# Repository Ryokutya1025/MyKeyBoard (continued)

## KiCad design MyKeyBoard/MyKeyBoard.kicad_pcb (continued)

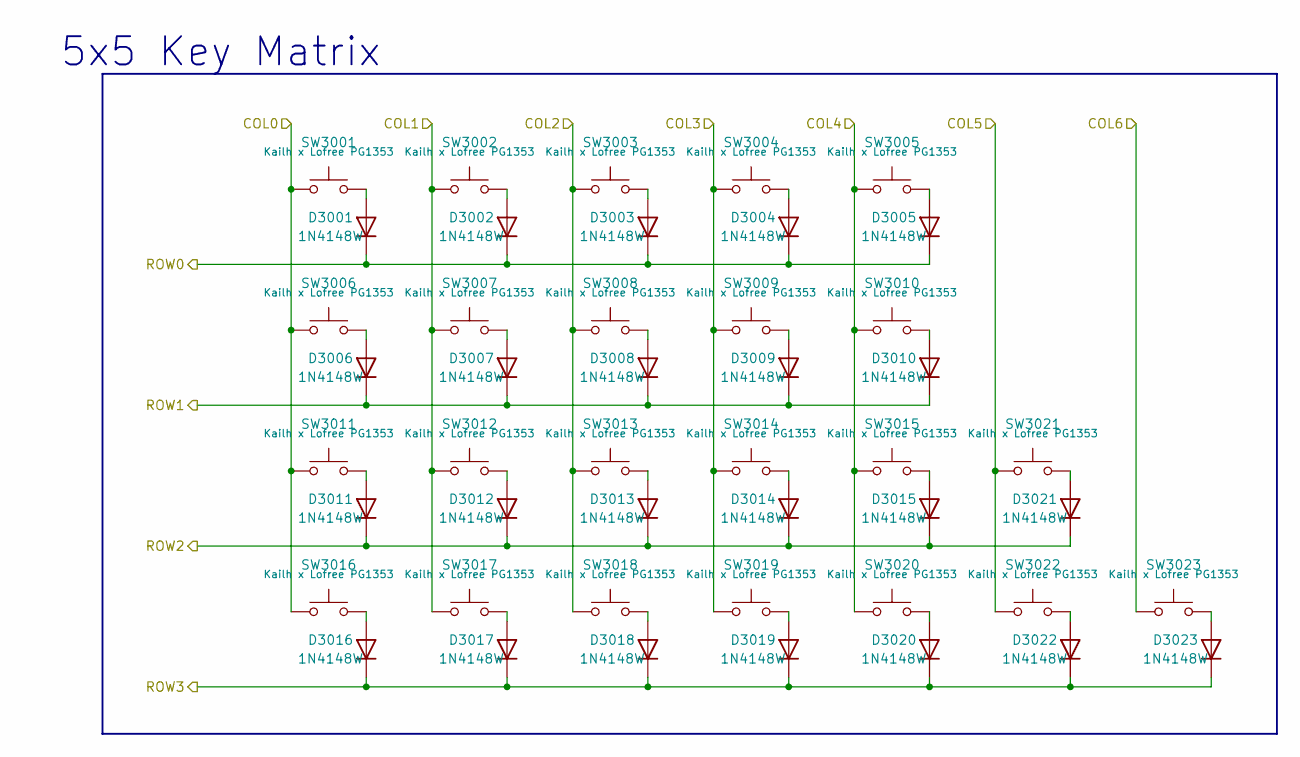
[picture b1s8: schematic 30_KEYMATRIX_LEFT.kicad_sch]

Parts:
D3001, D3002, D3003, D3004, D3005, D3006, D3007, D3008, D3009, D3010, D3011, D3012, D3013, D3014, D3015, D3016, D3017, D3018, D3019, D3020, D3021, D3022, D3023: 1N4148W; D_SOD-123
SW3001, SW3002, SW3003, SW3004, SW3005, SW3006, SW3007, SW3008, SW3009, SW3010, SW3011, SW3012, SW3013, SW3014, SW3015, SW3016, SW3017, SW3018, SW3019, SW3020, SW3021, SW3022, SW3023: Kailh x Lofree PG1353; Kailh-PG1353-Hotswap-1U

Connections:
/COL0_LEFT: SW3001.1, SW3006.1, SW3011.1, SW3016.1; also elsewhere on the board
/COL1_LEFT: SW3002.1, SW3007.1, SW3012.1, SW3017.1; also elsewhere on the board
/COL2_LEFT: SW3003.1, SW3008.1, SW3013.1, SW3018.1; also elsewhere on the board
/COL3_LEFT: SW3004.1, SW3009.1, SW3014.1, SW3019.1; also elsewhere on the board
/COL4_LEFT: SW3005.1, SW3010.1, SW3015.1, SW3020.1; also elsewhere on the board
/COL5_LEFT: SW3021.1, SW3022.1; also elsewhere on the board
/COL6_LEFT: SW3023.1; also elsewhere on the board
/ROW0_LEFT: D3001.1 (K), D3002.1 (K), D3003.1 (K), D3004.1 (K), D3005.1 (K); also elsewhere on the board
/ROW1_LEFT: D3006.1 (K), D3007.1 (K), D3008.1 (K), D3009.1 (K), D3010.1 (K); also elsewhere on the board
/ROW2_LEFT: D3011.1 (K), D3012.1 (K), D3013.1 (K), D3014.1 (K), D3015.1 (K), D3021.1 (K); also elsewhere on the board
/ROW3_LEFT: D3016.1 (K), D3017.1 (K), D3018.1 (K), D3019.1 (K), D3020.1 (K), D3022.1 (K), D3023.1 (K); also elsewhere on the board
unnamed: D3001.2 (A), SW3001.2
unnamed: D3002.2 (A), SW3002.2
unnamed: D3003.2 (A), SW3003.2
unnamed: D3004.2 (A), SW3004.2
unnamed: D3005.2 (A), SW3005.2
unnamed: D3006.2 (A), SW3006.2
unnamed: D3007.2 (A), SW3007.2
unnamed: D3008.2 (A), SW3008.2
unnamed: D3009.2 (A), SW3009.2
unnamed: D3010.2 (A), SW3010.2
unnamed: D3011.2 (A), SW3011.2
unnamed: D3012.2 (A), SW3012.2
unnamed: D3013.2 (A), SW3013.2
unnamed: D3014.2 (A), SW3014.2
unnamed: D3015.2 (A), SW3015.2
unnamed: D3016.2 (A), SW3016.2
unnamed: D3017.2 (A), SW3017.2
unnamed: D3018.2 (A), SW3018.2
unnamed: D3019.2 (A), SW3019.2
unnamed: D3020.2 (A), SW3020.2
unnamed: D3021.2 (A), SW3021.2
unnamed: D3022.2 (A), SW3022.2
unnamed: D3023.2 (A), SW3023.2

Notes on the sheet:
5x5 Key Matrix

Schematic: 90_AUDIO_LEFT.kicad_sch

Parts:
C9001: 10µF; C_0805_2012Metric
C9002: 100nF; C_0603_1608Metric
J9001: To Speaker; JST_SH_SM02B-SRSS-TB_1x02-1MP_P1.00mm_Horizontal_ToSpeaker
R9001: 1kΩ; R_0603_1608Metric
U9001: MAX98357A; TQFN-16-1EP_3x3mm_P0.5mm_EP1.23x1.23mm

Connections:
/+4V0_LEFT: C9001.1, C9002.1, U9001.7 (VDD), U9001.8 (VDD); also elsewhere on the board
/AUDIO_BCLK_LEFT: U9001.16 (BCLK); also elsewhere on the board
/AUDIO_DOUT_LEFT: U9001.1 (DIN); also elsewhere on the board
/AUDIO_LRCLK_LEFT: U9001.14 (LRCLK); also elsewhere on the board
/AUDIO_SD_LEFT: R9001.1; also elsewhere on the board
GND: C9001.2, C9002.2, U9001.3 (GND), U9001.11 (GND), U9001.15 (GND), U9001.17 (PAD); also elsewhere on the board
unnamed: J9001.1, U9001.9 (OUTP)
unnamed: J9001.2, U9001.10 (OUTN)
unnamed: R9001.2, U9001.4 (~SD_MODE)

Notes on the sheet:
Audio Amplifier

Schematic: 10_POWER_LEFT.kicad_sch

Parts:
C1001, C1002: 1µF; C_0603_1608Metric
C1003: 4.7µF; C_0805_2012Metric
C1004, C1005, C1007: 10µF; C_0805_2012Metric
C1006: 1nF; C_0603_1608Metric
C1008, C1009: 22µF; C_1206_3216Metric
C1010: 47µF; C_1210_3225Metric
C1011, C1012: 0.1µF; C_0603_1608Metric
D1001: LED_Dual_KAK; LED_LiteOn_LTST-S326
D1002: RED_LED; LED_0603_1608Metric
J1001: Battery; JST_PH_S3B-PH-SM4-TB_1x03-1MP_P2.00mm_Horizontal
J1002: USB_C_Receptacle_USB2.0_16P; USB_C_Receptacle_GCT_USB4105-xx-A_16P_TopMnt_Horizontal
L1001: 2.2µH; L_1008_2520Metric
L1002: 1µH; L_1008_2520Metric
Q1001: 2N7002; SOT-23
R1001, R1002, R1009: 1.5kΩ; R_0603_1608Metric
R1003, R1004: 5.1kΩ; R_0603_1608Metric
R1005, R1006: 27Ω; R_0603_1608Metric
R1007: 3.09kΩ; R_0603_1608Metric
R1008: 2.21kΩ; R_0603_1608Metric
R1010, R1015: 0Ω; R_0603_1608Metric
R1011, R1018: 1MΩ; R_0603_1608Metric
R1012: 100kΩ; R_0603_1608Metric
R1013: 634kΩ; R_0603_1608Metric
R1014: 16.2kΩ; R_0603_1608Metric
R1016: 36.5kΩ; R_0603_1608Metric
R1017: 91kΩ; R_0603_1608Metric
S1001: JS102011SAQN; SW_JS102011SAQN; DigiKey_Part_Number 401-1999-1-ND
TP1001: TP_3V3_LEFT; TestPoint_Pad_D1.5mm
U1001: TPS22919DCKR; MPN TPS22919DCKR
U1002: BQ24074RGT
U1003: TPD2E2U06DCK; SOT-323_SC-70
U1004: TPS631000DRLR; TPS631000DRLR_TEX-L
U1005: TPS63900; WSON-10-1EP_2.5x2.5mm_P0.5mm_EP1.2x2mm_ThermalVias
U1006: TXU0101DCKR; SC70-6_DCK_TEX

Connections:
/10_POWER_LEFT/BAT_NTC: J1001.2, U1002.1 (TS)
/10_POWER_LEFT/CHG_N: R1001.2, U1002.9 (~CHG)
/10_POWER_LEFT/PGOOD_N: R1002.2, U1002.7 (~PGOOD)
/10_POWER_LEFT/PWR_EN: R1018.2, S1001.2, U1004.5 (EN), U1005.1 (EN)
/10_POWER_LEFT/RGB_DATA_LED_LEFT: U1006.4 (BY); also elsewhere on the board
/10_POWER_LEFT/SYS_RAW: C1004.1, C1007.1, C1009.1, D1001.2 (A), S1001.3, U1002.10 (OUT), U1002.11 (OUT), U1004.4 (VIN), U1005.10 (VIN)
/10_POWER_LEFT/USB_SHIELD: C1006.2, J1002.SH (SHIELD), R1010.1, R1011.2
/+3V3_LEFT: C1008.1, C1011.1, R1009.1, TP1001.1 (1_1), U1005.6 (VOUT), U1006.1 (VCCA); also elsewhere on the board
/+4V0_LEFT: C1001.1, C1010.1, R1013.2, U1001.1 (VIN), U1004.1 (VOUT); also elsewhere on the board
/LOW_BAT_LED_LEFT: Q1001.1 (G), R1012.1; also elsewhere on the board
/RGB_DATA_MCU_LEFT: U1006.3 (A); also elsewhere on the board
/RGB_EN_LEFT: U1001.3 (ON), U1006.5 (OE); also elsewhere on the board
/RGB_VDD_LEFT: C1012.1, U1001.5 (QOD), U1001.6 (VOUT), U1006.6 (VCCB); also elsewhere on the board
/USB_DM_LEFT: R1005.2; also elsewhere on the board
/USB_DP_LEFT: R1006.1; also elsewhere on the board
/VBAT_LEFT: C1005.1, J1001.1, U1002.2 (BAT), U1002.3 (BAT); also elsewhere on the board
/VBUS_5V_LEFT: C1002.1, C1003.1, J1002.A4 (VBUS), J1002.A9 (VBUS), J1002.B4 (VBUS), J1002.B9 (VBUS), U1002.6 (EN1), U1002.13 (IN); also elsewhere on the board
GND: C1001.2, C1002.2, C1003.2, C1004.2, C1005.2, C1006.1, C1007.2, C1008.2, C1009.2, C1010.2, C1011.2, C1012.2, J1001.3, J1002.A1 (GND), J1002.A12 (GND), J1002.B1 (GND), J1002.B12 (GND), Q1001.2 (S), R1003.2, R1004.2, R1007.1, R1008.1, R1010.2, R1011.1, R1012.2, R1014.1, R1015.1, R1016.1, R1017.2, R1018.1, S1001.1, U1001.2 (GND), U1002.4 (~CE), U1002.5 (EN2), U1002.8 (VSS), U1002.17 (VSS), U1003.3, U1004.6 (MODE), U1004.7 (GND), U1005.2 (SEL), U1005.8 (GND), U1005.11 (GND), U1006.2 (GND); also elsewhere on the board
unnamed: D1001.1 (K1), R1001.1
unnamed: D1001.3 (K2), R1002.1
unnamed: D1002.2 (A), R1009.2
unnamed: D1002.1 (K), Q1001.3 (D)
unnamed: J1002.A5 (CC1), R1003.1
unnamed: J1002.B5 (CC2), R1004.1
unnamed: J1002.A6 (D+), J1002.B6 (D+), R1006.2, U1003.1
unnamed: J1002.A7 (D-), J1002.B7 (D-), R1005.1, U1003.2
unnamed: R1007.2, U1002.12 (ILIM)
unnamed: R1008.2, U1002.16 (ISET)
unnamed: R1013.1, R1017.1, U1004.8 (FB)
unnamed: L1002.1, U1004.3 (LX1)
unnamed: L1002.2, U1004.2 (LX2)
unnamed: R1016.2, U1005.3 (CFG1)
unnamed: R1015.2, U1005.4 (CFG2)
unnamed: R1014.2, U1005.5 (CFG3)
unnamed: L1001.1, U1005.9 (LX1)
unnamed: L1001.2, U1005.7 (LX2)

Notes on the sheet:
Battery Charger / Power Path
RGB Power Switch
USB Input / Protection
Main Power Switch
Main 3.3V Power
Low Battery LED
RGB 4.0V Power
Charge Status LED
RGB DATA Level Shifter

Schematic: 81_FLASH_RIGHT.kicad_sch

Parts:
C8101: 100nF; C_0603_1608Metric
R8101: 10kΩ; R_0603_1608Metric
U8101: W25Q512JVEIQ; PARTREV G; DigiKey_Part_Number 256-W25Q512JVEIQ-TUBE-ND

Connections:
/+3V3_RIGHT: C8101.1, R8101.1, U8101.8 (VCC); also elsewhere on the board
/FLASH_CLK_RIGHT: U8101.6 (CLK); also elsewhere on the board
/FLASH_CS_RIGHT: R8101.2, U8101.1 (~CS); also elsewhere on the board
/FLASH_I0_RIGHT: U8101.5 (IO0/DI); also elsewhere on the board
/FLASH_I1_RIGHT: U8101.2 (IO1/DO); also elsewhere on the board
/FLASH_I2_RIGHT: U8101.3 (IO2/~WP); also elsewhere on the board
/FLASH_I3_RIGHT: U8101.7 (IO3/~HOLD/~RESET); also elsewhere on the board
GND: C8101.2, U8101.4 (GND), U8101.9 (EXP); also elsewhere on the board

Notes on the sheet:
External Flash Memory

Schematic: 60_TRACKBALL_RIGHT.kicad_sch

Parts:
C6101: 3.3µF / 16V X7R; C_0805_2012Metric
C6102, C6103, C6104: 100nF X7R; C_0603_1608Metric
C6105: 10nF X7R; C_0603_1608Metric
C6106: 10nF; C_0603_1608Metric
C6107: 10µF; C_0805_2012Metric
TP6101: TP_TRACK_NRESET; TestPoint_Pad_D1.5mm
TP6102: TP_TRACK_MOTION; TestPoint_Pad_D1.5mm
TP6103: TP_TRACK_SCLK; TestPoint_Pad_D1.5mm
TP6104: TP_TRACK_SDIO; TestPoint_Pad_D1.5mm
TP6105: TP_TRACK_NCS; TestPoint_Pad_D1.5mm
U6101: PMW3610; PMW3610DM-SUDU 16Pin

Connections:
+1V8: C6101.1, C6102.1, U6101.14 (VDD); also elsewhere on the board
/+3V3_RIGHT: C6103.1, U6101.6 (VDDIO); also elsewhere on the board
/TRACK_MOTION: TP6102.1 (1_1), U6101.8 (MOTION); also elsewhere on the board
/TRACK_NCS: TP6105.1 (1_1), U6101.5 (NCS); also elsewhere on the board
/TRACK_NRESET: TP6101.1 (1_1), U6101.7 (NRESET); also elsewhere on the board
/TRACK_SCLK: TP6103.1 (1_1), U6101.3 (SCLK); also elsewhere on the board
/TRACK_SDIO: TP6104.1 (1_1), U6101.2 (SDIO); also elsewhere on the board
GND: C6101.2, C6102.2, C6103.2, C6105.2, C6106.2, C6107.2, U6101.11 (GND); also elsewhere on the board
unnamed: C6105.1, U6101.1 (+VCSEL), U6101.10 (PASS_T)
unnamed: U6101.15 (XYLASER), U6101.16 (-VCSEL)
unnamed: C6104.1, U6101.13 (CN)
unnamed: C6104.2, U6101.12 (CP)
unnamed: C6106.1, C6107.1, U6101.9 (VCP)

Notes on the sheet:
Trackball Sensor

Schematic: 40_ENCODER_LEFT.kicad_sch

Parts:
C4001, C4002, C4003: 10nF; C_0603_1608Metric
R4001, R4003, R4006: 10kΩ; R_0603_1608Metric
R4002, R4004, R4005: 1kΩ; R_0603_1608Metric
SW4001: SKQYACE010
SW4002: RotaryEncoder; EC05E1220202

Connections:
/+3V3_LEFT: R4001.2, R4003.1, R4006.1; also elsewhere on the board
/ENC_A_LEFT: C4003.1, R4004.1; also elsewhere on the board
/ENC_B_LEFT: C4002.1, R4005.1; also elsewhere on the board
/ENC_SW_LEFT: C4001.1, R4001.1, R4002.1; also elsewhere on the board
GND: C4001.2, C4002.2, C4003.2, SW4001.2, SW4002.C; also elsewhere on the board
unnamed: R4002.2, SW4001.1
unnamed: R4003.2, R4004.2, SW4002.A
unnamed: R4005.2, R4006.2, SW4002.B

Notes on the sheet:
Horizontal Encoder + Click

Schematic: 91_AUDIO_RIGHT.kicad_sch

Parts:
C9101: 10µF; C_0805_2012Metric
C9102: 100nF; C_0603_1608Metric
J9101: To Speaker; JST_SH_SM02B-SRSS-TB_1x02-1MP_P1.00mm_Horizontal_ToSpeaker
R9101: 1kΩ; R_0603_1608Metric
U9101: MAX98357A; TQFN-16-1EP_3x3mm_P0.5mm_EP1.23x1.23mm

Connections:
/+4V0_RIGHT: C9101.1, C9102.1, U9101.7 (VDD), U9101.8 (VDD); also elsewhere on the board
/AUDIO_BCLK_RIGHT: U9101.16 (BCLK); also elsewhere on the board
/AUDIO_DOUT_RIGHT: U9101.1 (DIN); also elsewhere on the board
/AUDIO_LRCLK_RIGHT: U9101.14 (LRCLK); also elsewhere on the board
/AUDIO_SD_RIGHT: R9101.1; also elsewhere on the board
GND: C9101.2, C9102.2, U9101.3 (GND), U9101.11 (GND), U9101.15 (GND), U9101.17 (PAD); also elsewhere on the board
unnamed: J9101.1, U9101.9 (OUTP)
unnamed: J9101.2, U9101.10 (OUTN)
unnamed: R9101.2, U9101.4 (~SD_MODE)

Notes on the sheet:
Audio Amplifier

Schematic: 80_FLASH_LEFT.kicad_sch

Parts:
C8001: 100nF; C_0603_1608Metric
R8001: 10kΩ; R_0603_1608Metric
U8001: W25Q512JVEIQ; PARTREV G; DigiKey_Part_Number 256-W25Q512JVEIQ-TUBE-ND

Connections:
/+3V3_LEFT: C8001.1, R8001.1, U8001.8 (VCC); also elsewhere on the board
/FLASH_CLK_LEFT: U8001.6 (CLK); also elsewhere on the board
/FLASH_CS_LEFT: R8001.2, U8001.1 (~CS); also elsewhere on the board
/FLASH_I0_LEFT: U8001.5 (IO0/DI); also elsewhere on the board
/FLASH_I1_LEFT: U8001.2 (IO1/DO); also elsewhere on the board
/FLASH_I2_LEFT: U8001.3 (IO2/~WP); also elsewhere on the board
/FLASH_I3_LEFT: U8001.7 (IO3/~HOLD/~RESET); also elsewhere on the board
GND: C8001.2, U8001.4 (GND), U8001.9 (EXP); also elsewhere on the board

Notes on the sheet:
External Flash Memory

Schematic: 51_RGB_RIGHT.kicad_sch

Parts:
C5101: 47µF; C_1210_3225Metric
C5102, C5103, C5104, C5105, C5106, C5107, C5108, C5109, C5110, C5111, C5112, C5113, C5114, C5115, C5116, C5117, C5118, C5119, C5120, C5121, C5122: 100nF; C_0603_1608Metric
D5101, D5102, D5103, D5104, D5105, D5106, D5107, D5108, D5109, D5110, D5111, D5112, D5113, D5114, D5115, D5116, D5117, D5118, D5119, D5120, D5121: SK6805MINI-E; SK6812MINI-E
R5101: 100Ω; R_0603_1608Metric

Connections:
/11_POWER_RIGHT/RGB_DATA_LED_RIGHT: R5101.1; also elsewhere on the board
/51_RGB_RIGHT/RGB_DATA_08to09: D5108.4 (DOUT), D5109.2 (DIN)
/51_RGB_RIGHT/RGB_DATA_16to17: D5116.4 (DOUT), D5117.2 (DIN)
/RGB_VDD_RIGHT: C5101.1, C5102.1, C5103.1, C5104.1, C5105.1, C5106.1, C5107.1, C5108.1, C5109.1, C5110.1, C5111.1, C5112.1, C5113.1, C5114.1, C5115.1, C5116.1, C5117.1, C5118.1, C5119.1, C5120.1, C5121.1, C5122.1, D5101.3 (VDD), D5102.3 (VDD), D5103.3 (VDD), D5104.3 (VDD), D5105.3 (VDD), D5106.3 (VDD), D5107.3 (VDD), D5108.3 (VDD), D5109.3 (VDD), D5110.3 (VDD), D5111.3 (VDD), D5112.3 (VDD), D5113.3 (VDD), D5114.3 (VDD), D5115.3 (VDD), D5116.3 (VDD), D5117.3 (VDD), D5118.3 (VDD), D5119.3 (VDD), D5120.3 (VDD), D5121.3 (VDD); also elsewhere on the board
GND: C5101.2, C5102.2, C5103.2, C5104.2, C5105.2, C5106.2, C5107.2, C5108.2, C5109.2, C5110.2, C5111.2, C5112.2, C5113.2, C5114.2, C5115.2, C5116.2, C5117.2, C5118.2, C5119.2, C5120.2, C5121.2, C5122.2, D5101.1 (VSS), D5102.1 (VSS), D5103.1 (VSS), D5104.1 (VSS), D5105.1 (VSS), D5106.1 (VSS), D5107.1 (VSS), D5108.1 (VSS), D5109.1 (VSS), D5110.1 (VSS), D5111.1 (VSS), D5112.1 (VSS), D5113.1 (VSS), D5114.1 (VSS), D5115.1 (VSS), D5116.1 (VSS), D5117.1 (VSS), D5118.1 (VSS), D5119.1 (VSS), D5120.1 (VSS), D5121.1 (VSS); also elsewhere on the board
unnamed: D5101.2 (DIN), R5101.2
unnamed: D5101.4 (DOUT), D5102.2 (DIN)
unnamed: D5102.4 (DOUT), D5103.2 (DIN)
unnamed: D5103.4 (DOUT), D5104.2 (DIN)
unnamed: D5104.4 (DOUT), D5105.2 (DIN)
unnamed: D5105.4 (DOUT), D5106.2 (DIN)
unnamed: D5106.4 (DOUT), D5107.2 (DIN)
unnamed: D5107.4 (DOUT), D5108.2 (DIN)
unnamed: D5109.4 (DOUT), D5110.2 (DIN)
unnamed: D5110.4 (DOUT), D5111.2 (DIN)
unnamed: D5111.4 (DOUT), D5112.2 (DIN)
unnamed: D5112.4 (DOUT), D5113.2 (DIN)
unnamed: D5113.4 (DOUT), D5114.2 (DIN)
unnamed: D5114.4 (DOUT), D5115.2 (DIN)
unnamed: D5115.4 (DOUT), D5116.2 (DIN)
unnamed: D5117.4 (DOUT), D5118.2 (DIN)
unnamed: D5118.4 (DOUT), D5119.2 (DIN)
unnamed: D5119.4 (DOUT), D5120.2 (DIN)
unnamed: D5120.4 (DOUT), D5121.2 (DIN)

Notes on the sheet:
Addressable RGB LED Chain

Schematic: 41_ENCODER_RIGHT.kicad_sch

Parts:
C4101, C4102, C4103: 10nF; C_0603_1608Metric
R4101, R4103, R4106: 10kΩ; R_0603_1608Metric
R4102, R4104, R4105: 1kΩ; R_0603_1608Metric
SW4101: SKQYACE010
SW4102: RotaryEncoder; EC05E1220202

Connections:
/+3V3_RIGHT: R4101.2, R4103.1, R4106.1; also elsewhere on the board
/ENC_A_RIGHT: C4103.1, R4104.1; also elsewhere on the board
/ENC_B_RIGHT: C4102.1, R4105.1; also elsewhere on the board
/ENC_SW_RIGHT: C4101.1, R4101.1, R4102.1; also elsewhere on the board
GND: C4101.2, C4102.2, C4103.2, SW4101.2, SW4102.C; also elsewhere on the board
unnamed: R4102.2, SW4101.1
unnamed: R4103.2, R4104.2, SW4102.A
unnamed: R4105.2, R4106.2, SW4102.B

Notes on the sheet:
Horizontal Encoder + Click

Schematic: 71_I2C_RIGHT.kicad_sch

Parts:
AC7101: LIS2DTW12TR; LGA-12_2x2mm_P0.5mm; Mouser Part Number 511-LIS2DTW12TR
C7101, C7102, C7103, C7104, C7106: 100nF; C_0603_1608Metric
C7105: 10µF; C_0805_2012Metric
R7101, R7102: 3.3kΩ; R_0603_1608Metric
R7103: 10kΩ; R_0603_1608Metric
R7104: 1000Ω; R_0603_1608Metric
U7101: MAX17048G+
U7102: RV-3028-C7

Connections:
/+3V3_RIGHT: AC7101.2 (CS), AC7101.9 (VDD), AC7101.10 (VDDIO), C7101.1, C7104.1, C7105.1, C7106.1, R7101.2, R7102.2, U7102.7 (VDD); also elsewhere on the board
/ACC_INT_RIGHT: AC7101.12 (INT1); also elsewhere on the board
/I2C_SCL_RIGHT: AC7101.1 (SCL/SPC), R7101.1, U7101.7 (SCL), U7102.3 (SCL); also elsewhere on the board
/I2C_SDA_RIGHT: AC7101.4 (SDA/SDI/SDO), R7102.1, U7101.8 (SDA), U7102.4 (SDA); also elsewhere on the board
/VBAT_RIGHT: C7102.1, R7104.2, U7101.2 (CELL), U7101.3 (VDD); also elsewhere on the board
GND: AC7101.3 (SDO/SA0), AC7101.6 (GND_1), AC7101.7 (RES), AC7101.8 (GND_2), C7101.2, C7102.2, C7103.2, C7104.2, C7105.2, C7106.2, R7103.2, U7101.1 (CTG), U7101.4 (GND), U7101.6 (QSTRT), U7101.9 (EPAD), U7102.5 (VSS); also elsewhere on the board
unnamed: R7103.1, U7102.8 (EVI)
unnamed: C7103.1, R7104.1, U7102.6 (VBACKUP)

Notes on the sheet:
RTC and I2C Bus
Motion Sensor
Battery Fuel Gauge

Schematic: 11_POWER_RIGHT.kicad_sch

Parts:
C1101, C1102, C1111, C1112: 1µF; C_0603_1608Metric
C1103: 4.7µF; C_0805_2012Metric
C1104, C1105, C1107: 10µF; C_0805_2012Metric
C1106: 1nF; C_0603_1608Metric
C1108, C1109: 22µF; C_1206_3216Metric
C1110: 47µF; C_1210_3225Metric
C1113, C1114: 0.1µF; C_0603_1608Metric
D1101: LED_Dual_KAK; LED_LiteOn_LTST-S326
D1102: RED_LED; LED_0603_1608Metric
J1101: Battery; JST_PH_S3B-PH-SM4-TB_1x03-1MP_P2.00mm_Horizontal
J1102: USB_C_Receptacle_USB2.0_16P; USB_C_Receptacle_GCT_USB4105-xx-A_16P_TopMnt_Horizontal
L1101: 2.2µH; L_1008_2520Metric
L1102: 1µH; L_1008_2520Metric
Q1101: 2N7002; SOT-23
R1101, R1102, R1109: 1.5kΩ; R_0603_1608Metric
R1103, R1104: 5.1kΩ; R_0603_1608Metric
R1105, R1106: 27Ω; R_0603_1608Metric
R1107: 3.09kΩ; R_0603_1608Metric
R1108: 2.21kΩ; R_0603_1608Metric
R1110, R1115: 0Ω; R_0603_1608Metric
R1111, R1118: 1MΩ; R_0603_1608Metric
R1112: 100kΩ; R_0603_1608Metric
R1113: 634kΩ; R_0603_1608Metric
R1114: 16.2kΩ; R_0603_1608Metric
R1116: 36.5kΩ; R_0603_1608Metric
R1117: 91kΩ; R_0603_1608Metric
S1101: JS102011SAQN; SW_JS102011SAQN; DigiKey_Part_Number 401-1999-1-ND
TP1101: TP_3V3_RIGHT; TestPoint_Pad_D1.5mm
TP1102: TP_1V8_RIGHT; TestPoint_Pad_D1.5mm
U1101: TPS22919DCKR; MPN TPS22919DCKR
U1102: BQ24074RGT
U1103: TPD2E2U06DCK; SOT-323_SC-70
U1104: TPS631000DRLR; TPS631000DRLR_TEX-L
U1105: TLV74318PDBVR
U1106: TPS63900; WSON-10-1EP_2.5x2.5mm_P0.5mm_EP1.2x2mm_ThermalVias
U1107: TXU0101DCKR; SC70-6_DCK_TEX

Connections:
+1V8: C1112.1, TP1102.1 (1_1), U1105.5 (OUT); also elsewhere on the board
/11_POWER_RIGHT/BAT_NTC: J1101.2, U1102.1 (TS)
/11_POWER_RIGHT/CHG_N: R1101.2, U1102.9 (~CHG)
/11_POWER_RIGHT/PGOOD_N: R1102.2, U1102.7 (~PGOOD)
/11_POWER_RIGHT/PWR_EN: R1118.2, S1101.2, U1104.5 (EN), U1106.1 (EN)
/11_POWER_RIGHT/RGB_DATA_LED_RIGHT: U1107.4 (BY); also elsewhere on the board
/11_POWER_RIGHT/SYS_RAW: C1104.1, C1107.1, C1109.1, D1101.2 (A), S1101.3, U1102.10 (OUT), U1102.11 (OUT), U1104.4 (VIN), U1106.10 (VIN)
/11_POWER_RIGHT/USB_SHIELD: C1106.2, J1102.SH (SHIELD), R1110.1, R1111.2
/+3V3_RIGHT: C1108.1, C1111.1, C1113.1, R1109.1, TP1101.1 (1_1), U1105.1 (IN), U1105.3 (EN), U1106.6 (VOUT), U1107.1 (VCCA); also elsewhere on the board
/+4V0_RIGHT: C1101.1, C1110.1, R1113.2, U1101.1 (VIN), U1104.1 (VOUT); also elsewhere on the board
/LOW_BAT_LED_RIGHT: Q1101.1 (G), R1112.1; also elsewhere on the board
/RGB_DATA_MCU_RIGHT: U1107.3 (A); also elsewhere on the board
/RGB_EN_RIGHT: U1101.3 (ON), U1107.5 (OE); also elsewhere on the board
/RGB_VDD_RIGHT: C1114.1, U1101.5 (QOD), U1101.6 (VOUT), U1107.6 (VCCB); also elsewhere on the board
/USB_DM_RIGHT: R1105.2; also elsewhere on the board
/USB_DP_RIGHT: R1106.1; also elsewhere on the board
/VBAT_RIGHT: C1105.1, J1101.1, U1102.2 (BAT), U1102.3 (BAT); also elsewhere on the board
/VBUS_5V_RIGHT: C1102.1, C1103.1, J1102.A4 (VBUS), J1102.A9 (VBUS), J1102.B4 (VBUS), J1102.B9 (VBUS), U1102.6 (EN1), U1102.13 (IN); also elsewhere on the board
GND: C1101.2, C1102.2, C1103.2, C1104.2, C1105.2, C1106.1, C1107.2, C1108.2, C1109.2, C1110.2, C1111.2, C1112.2, C1113.2, C1114.2, J1101.3, J1102.A1 (GND), J1102.A12 (GND), J1102.B1 (GND), J1102.B12 (GND), Q1101.2 (S), R1103.2, R1104.2, R1107.1, R1108.1, R1110.2, R1111.1, R1112.2, R1114.1, R1115.1, R1116.1, R1117.2, R1118.1, S1101.1, U1101.2 (GND), U1102.4 (~CE), U1102.5 (EN2), U1102.8 (VSS), U1102.17 (VSS), U1103.3, U1104.6 (MODE), U1104.7 (GND), U1105.2 (GND), U1106.2 (SEL), U1106.8 (GND), U1106.11 (GND), U1107.2 (GND); also elsewhere on the board
unnamed: D1101.1 (K1), R1101.1
unnamed: D1101.3 (K2), R1102.1
unnamed: D1102.2 (A), R1109.2
unnamed: D1102.1 (K), Q1101.3 (D)
unnamed: J1102.A5 (CC1), R1103.1
unnamed: J1102.B5 (CC2), R1104.1
unnamed: J1102.A6 (D+), J1102.B6 (D+), R1106.2, U1103.1
unnamed: J1102.A7 (D-), J1102.B7 (D-), R1105.1, U1103.2
unnamed: R1107.2, U1102.12 (ILIM)
unnamed: R1108.2, U1102.16 (ISET)
unnamed: R1113.1, R1117.1, U1104.8 (FB)
unnamed: L1102.1, U1104.3 (LX1)
unnamed: L1102.2, U1104.2 (LX2)
unnamed: R1116.2, U1106.3 (CFG1)
unnamed: R1115.2, U1106.4 (CFG2)
unnamed: R1114.2, U1106.5 (CFG3)
unnamed: L1101.1, U1106.9 (LX1)
unnamed: L1101.2, U1106.7 (LX2)

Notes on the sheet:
Main Power Switch
RGB DATA Level Shifter
USB Input / Protection
Main 3.3V Power
Charge Status LED
Low Battery LED
Battery Charger / Power Path
RGB Power Switch
RGB 4.0V Power
Trackball 1.8V Power

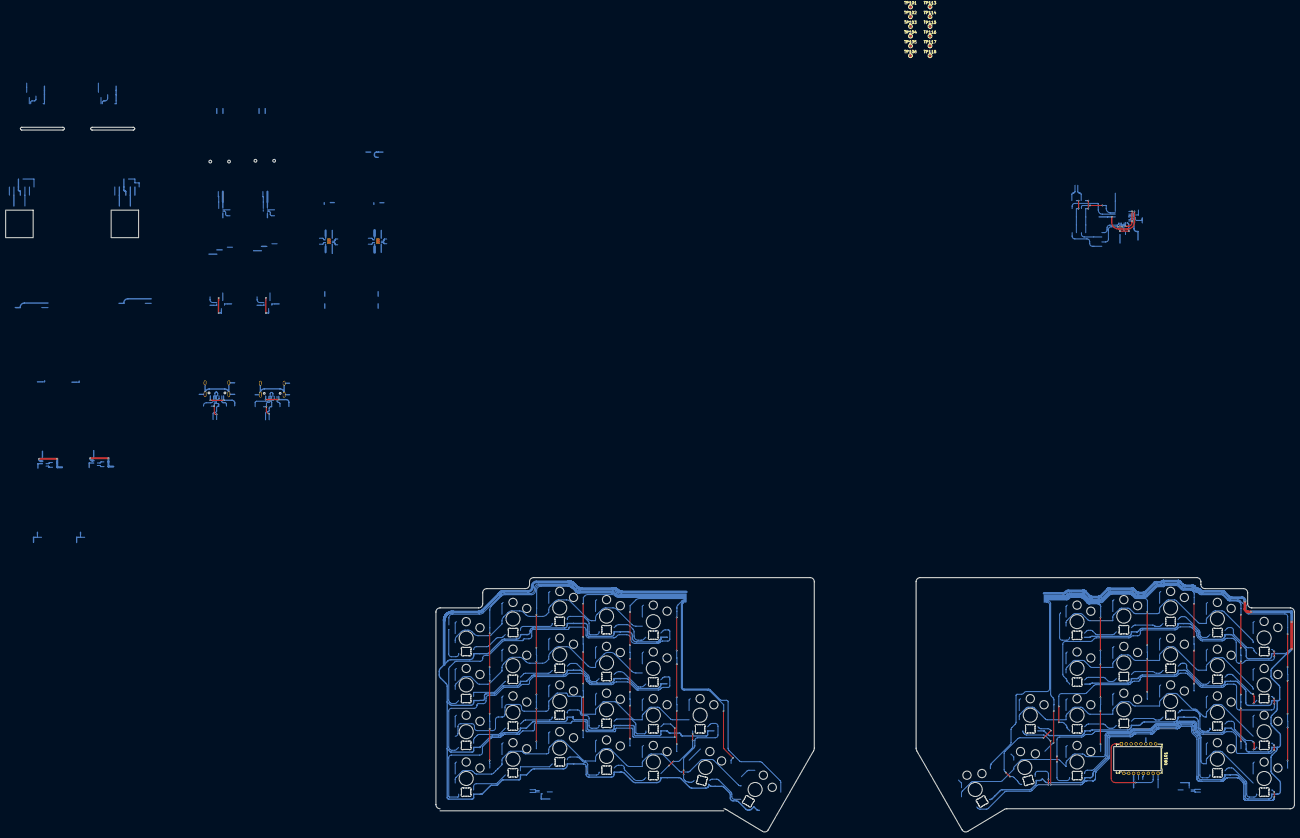
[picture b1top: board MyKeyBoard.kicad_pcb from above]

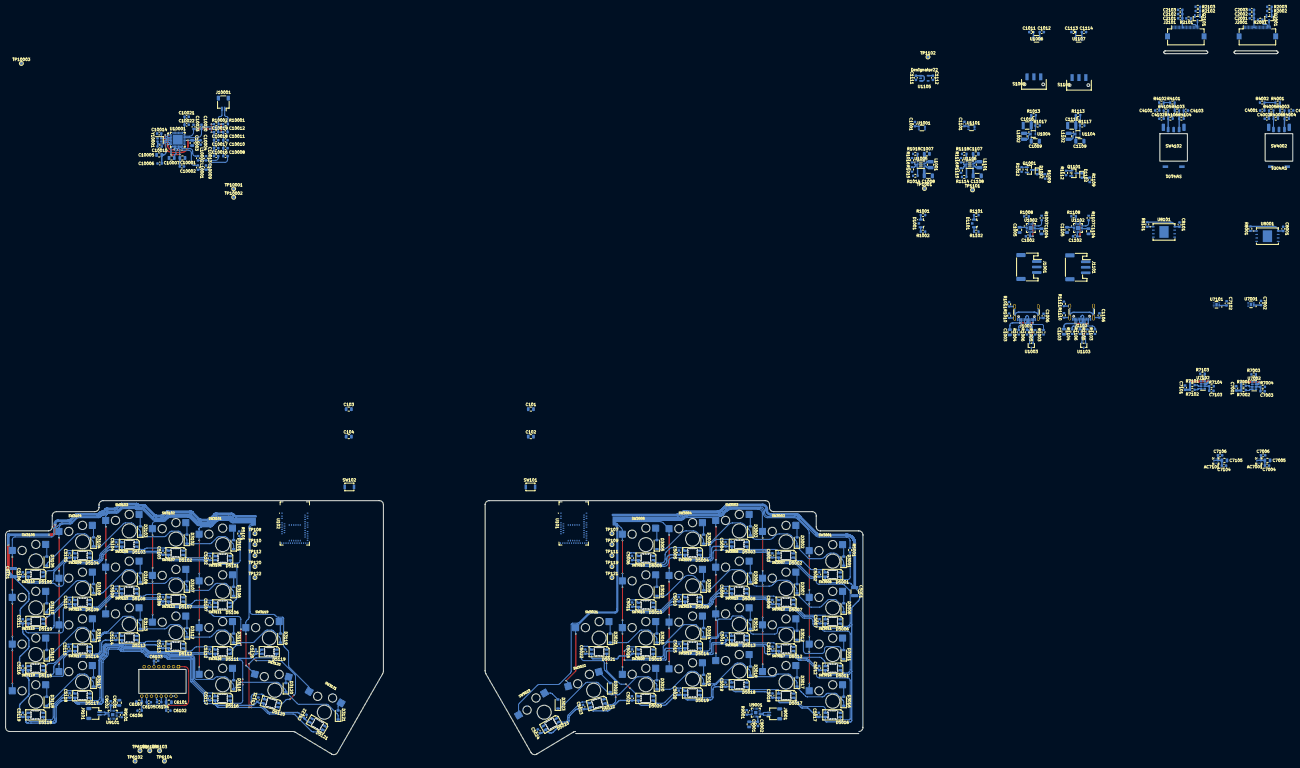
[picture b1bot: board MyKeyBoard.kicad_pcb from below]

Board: 2 copper layers, 468.4 x 256.1 mm, 430 parts (329 on the bottom side), 284 nets.
